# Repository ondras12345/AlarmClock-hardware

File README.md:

# AlarmClock Hardware
This repository contains hardware design files for [AlarmClock][AlarmClock].

Schematics and PCBs are designed in [KiCAD][KiCAD].

[AlarmClock]: https://github.com/ondras12345/AlarmClock
[KiCAD]: https://www.kicad.org/

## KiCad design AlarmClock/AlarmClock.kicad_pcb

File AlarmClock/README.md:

# AlarmClock
This is the main project for the whole thing. Both schematics and PCB design.

[Schematics](./AlarmClock.pdf)
[PCB](./AlarmClock-PCB.pdf)

The PCB is designed to be milled out from a single sided copper clad laminate
on a CNC machine. However, the design should also be suitable for standard
etching.

**Warning**: R27 is currently NOT included in the gcode files in `cnc/`.
However, it is quite easy to bodge in if you don't want to mess with `FlatCAM`
to fix this. Gerber files are OK.

## MCU pinout
Pin numbers in the firmware are using the convention set by the Arduino
framework. To map them to MCU pins, use the following table:

|Arduino pin    | MCU pin   |
|:--------------|:----------|
| 0             | PD0       |
| 1             | PD1       |
| 2             | PD2       |
| 3             | PD3       |
| 4             | PD4       |
| 5             | PD5       |
| 6             | PD6       |
| 7             | PD7       |
| 8             | PB0       |
| 9             | PB1       |
| 10            | PB2       |
| 11            | PB3       |
| 12            | PB4       |
| 13            | PB5       |
| A0            | PC0       |
| A1            | PC1       |
| A2            | PC2       |
| A3            | PC3       |
| A4            | PC4       |
| A5            | PC5       |

- https://www.arduino.cc/en/uploads/Main/Arduino_Uno_Rev3-schematic.pdf

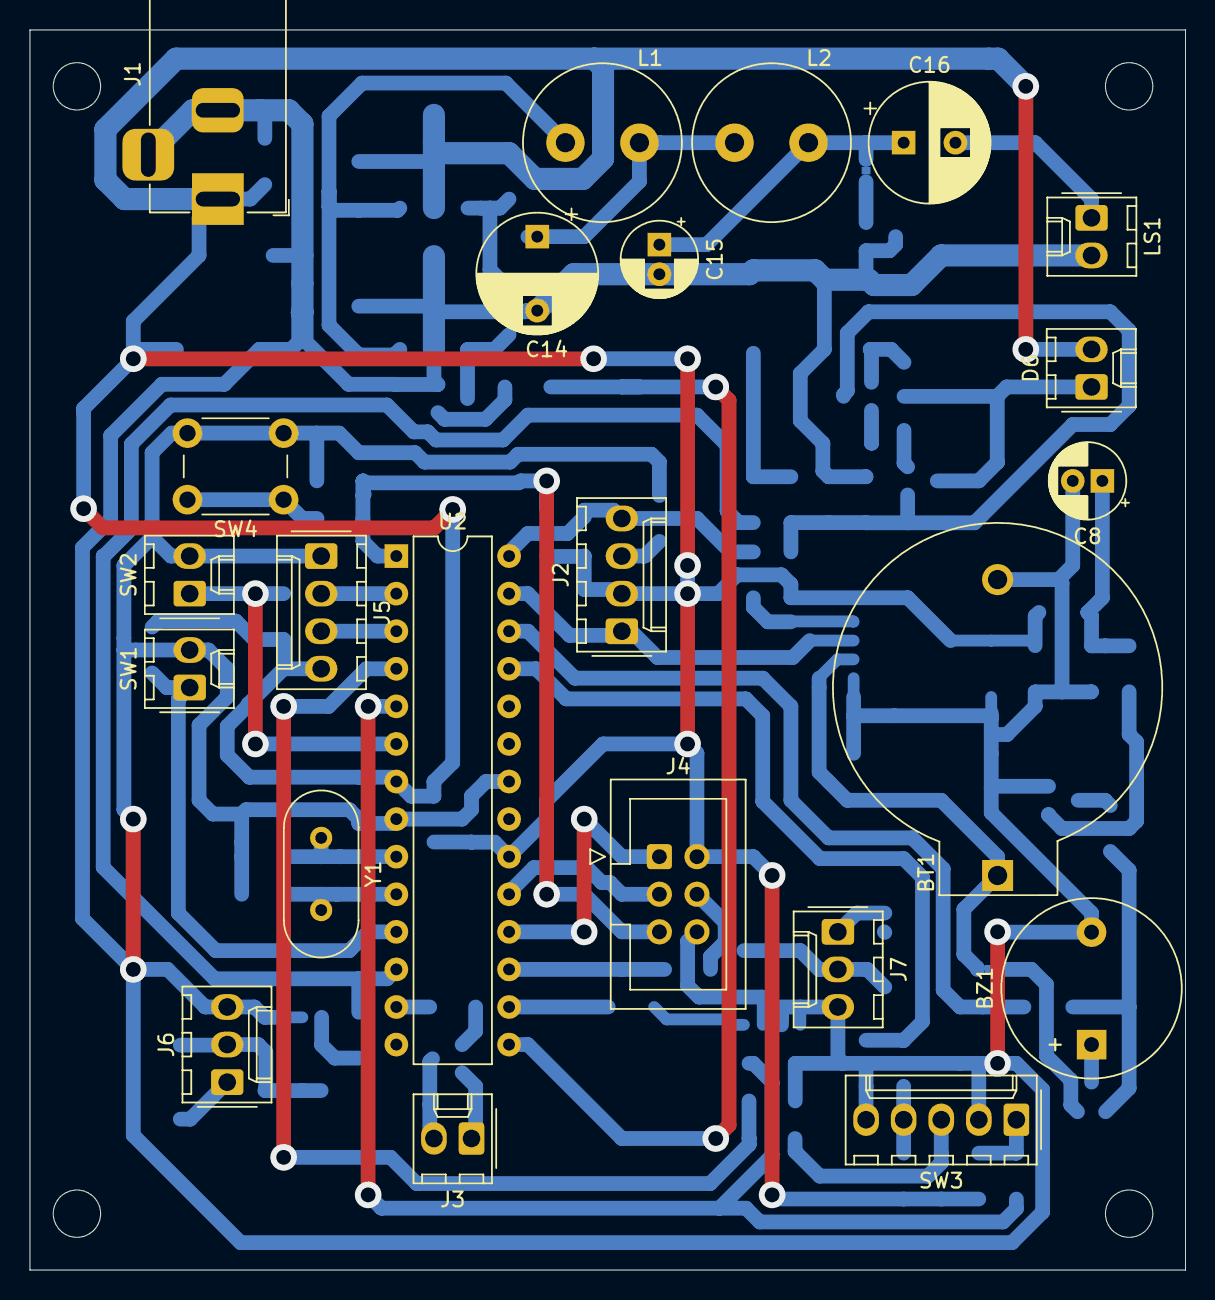
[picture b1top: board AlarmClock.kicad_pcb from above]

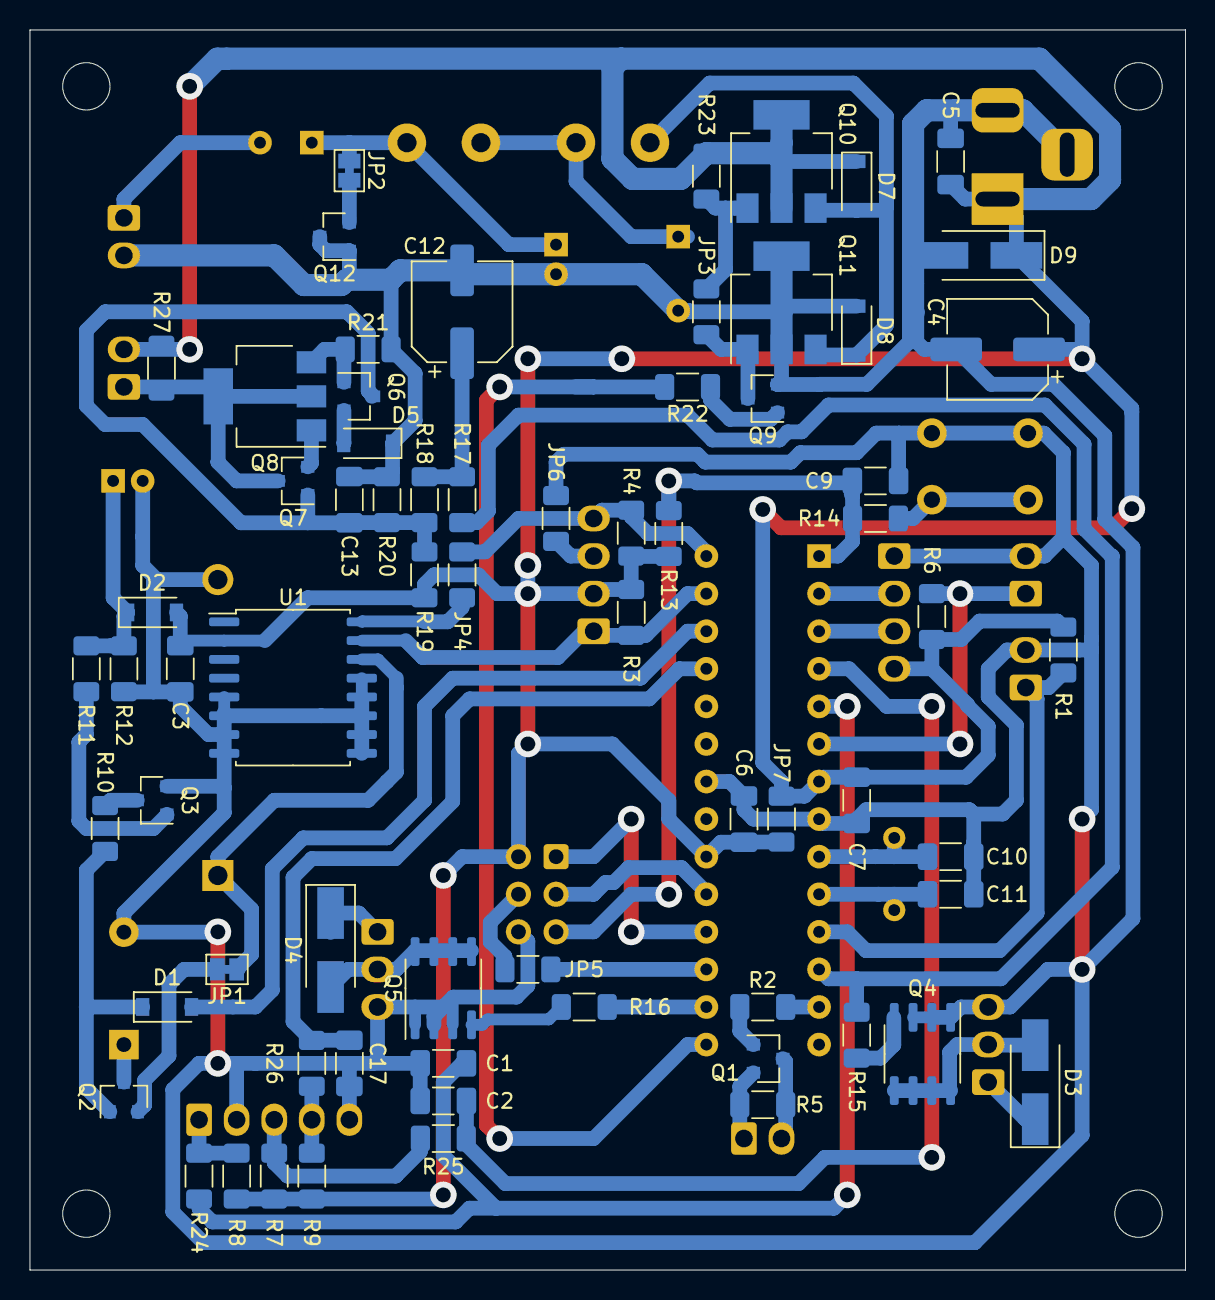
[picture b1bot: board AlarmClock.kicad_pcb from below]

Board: 2 copper layers, 78.1 x 83.8 mm, 91 parts (68 on the bottom side), 59 nets.

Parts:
BT1: CR2032; BatteryHolder_DS1092-04-B6P
BZ1: 3V3; Buzzer_12x9.5RM7.6
C1, C2: 10n; C_1206_3216Metric_Pad1.33x1.80mm_HandSolder
C3, C7, C9, C13, C17: 100n; C_1206_3216Metric_Pad1.33x1.80mm_HandSolder
C4, C12: 100u / 16V; CP_Elec_6.3x5.4
C5: 470n; C_1206_3216Metric_Pad1.33x1.80mm_HandSolder
C6: 1u / 25V; C_1206_3216Metric_Pad1.33x1.80mm_HandSolder
C8: 22u / 35V; CP_Radial_D5.0mm_P2.00mm
C10, C11: 22p; C_1206_3216Metric_Pad1.33x1.80mm_HandSolder
C14: 3u3 / 50V; CP_Radial_D8.0mm_P5.00mm
C15: 1u / 50V; CP_Radial_D5.0mm_P2.00mm
C16: 220u / 35V; CP_Radial_D8.0mm_P3.50mm
D1, D2, D5, D7, D8: 1N4148W; D_SOD-123
D3, D4, D9: 1N4007; D_SMA_Handsoldering
D6: LED; Molex_KK-254_AE-6410-02A_1x02_P2.54mm_Vertical
J1: PC-GK2.1; BarrelJack_Horizontal
J2, J5: Conn_01x04; Molex_KK-254_AE-6410-04A_1x04_P2.54mm_Vertical
J3: Conn_01x02; Molex_KK-254_AE-6410-02A_1x02_P2.54mm_Vertical
J4: AVR-ISP-6; IDC-Header_2x03_P2.54mm_Vertical
J6, J7: Conn_01x03; Molex_KK-254_AE-6410-03A_1x03_P2.54mm_Vertical
JP1, JP2: SolderJumper_2_Bridged; SolderJumper-2_P1.3mm_Bridged_Pad1.0x1.5mm
JP3, JP4, JP5, JP6, JP7: 0 ohm; R_1206_3216Metric_Pad1.30x1.75mm_HandSolder
L1: 220u; L_Radial_D10.5mm_P5.00mm_Abacron_AISR-01
L2: 100u; L_Radial_D10.5mm_P5.00mm_Abacron_AISR-01
LS1: 8 ohm; Molex_KK-254_AE-6410-02A_1x02_P2.54mm_Vertical
Q1: BC857; SOT-23
Q2: BC857B; SOT-23
Q3, Q6, Q7, Q9, Q12: BC847; SOT-23
Q4, Q5: IRL6342PbF; SOIC-8_3.9x4.9mm_P1.27mm
Q8, Q10: BCP56; SOT-223-3_TabPin2
Q11: BCP53; SOT-223-3_TabPin2
R1, R2, R6, R7, R8, R9, R10, R13, R18, R20, R24, R25, R26, R27: 10k; R_1206_3216Metric_Pad1.30x1.75mm_HandSolder
R3, R4, R5: 3k3; R_1206_3216Metric_Pad1.30x1.75mm_HandSolder
R11, R12: 100k; R_1206_3216Metric_Pad1.30x1.75mm_HandSolder
R14, R23: 330; R_1206_3216Metric_Pad1.30x1.75mm_HandSolder
R15, R16: 220; R_1206_3216Metric_Pad1.30x1.75mm_HandSolder
R17, R22: 1k; R_1206_3216Metric_Pad1.30x1.75mm_HandSolder
R19: 22k; R_1206_3216Metric_Pad1.30x1.75mm_HandSolder
R21: 6R8; R_1206_3216Metric_Pad1.30x1.75mm_HandSolder
SW1, SW2: SW_Push; Molex_KK-254_AE-6410-02A_1x02_P2.54mm_Vertical
SW3: Rotary_Encoder_Switch; Rotary_Encode_Switch_Molex_KK-254_AE-6410-05A_1x05_P2.54mm_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
SW4: SW_Push; SW_PUSH_6mm_H4.3mm
U1: DS3231M; SOIC-16W_7.5x10.3mm_P1.27mm
U2: ATmega328P-PU; DIP-28_W7.62mm
Y1: 16MHz; Crystal_HC49-U_Vertical

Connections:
+5V: C3.1, C4.1, C5.1, C6.1, C7.1, D2.2, D6.2, D7.1, D9.1, J1.1, J2.2, J4.2, J5.4, JP7.1, JP7.2, Q10.2, R1.1, R3.1, R4.1, R6.1, R7.1, R8.1, R9.1, R13.1, R19.1, R23.1, R27.1, U1.2, U2.7, U2.20
/!RST: C9.1, J4.5, R13.2, R14.2, U2.1
/BTN_snooze: R6.2, SW2.1, U2.6
/BTN_stop: R1.2, SW1.1, U2.11
/LCD_BLU: R2.2, U2.13
/MISO: J4.1, U2.18
/MOSI: JP5.2, U2.17
/RX: J5.2, U2.2
/SCK: J4.3, U2.19
/SCL: J2.4, JP4.1, R4.2, U2.28
/SDA: J2.1, R3.2, U1.15, U2.27
/TX: J5.3, U2.3
/ambient: R15.2, R17.2, U2.12
/audio: R22.2, U2.15
/buzzer: D1.2, U2.26
/enc_clk: C2.1, R25.2, U2.4
/enc_dt: C1.1, R24.2, U2.5
/enc_sw: C17.1, R26.1, U2.25
/lamp: R16.2, U2.16
GND: BT1.2, BZ1.2, C1.2, C2.2, C3.2, C4.2, C5.2, C6.2, C7.2, C8.2, C9.2, C10.1, C11.2, C12.2, C13.2, C14.2, C15.2, C17.2, D5.1, D8.2, D9.2, J1.2, J1.3, J4.6, J5.1, J6.3, J7.3, JP6.1, LS1.2, Q3.2, Q4.1, Q4.2, Q4.3, Q5.1, Q5.2, Q5.3, Q9.2, Q11.2, Q12.1, Q12.3, R12.2, R20.2, R21.2, SW1.2, SW2.2, SW3.C, SW3.S2, SW4.2, U1.5, U1.6, U1.7, U1.8, U1.9, U1.10, U1.11, U1.12, U1.13, U2.8, U2.22
unnamed: BT1.1, JP1.1, U1.14
unnamed: BZ1.1, Q2.3
unnamed: C8.1, D2.1, R11.1, R12.1
unnamed: C10.2, U2.9, Y1.1
unnamed: C11.1, U2.10, Y1.2
unnamed: C12.1, R17.1, R18.2
unnamed: C13.1, Q6.3, Q7.1, R18.1, R19.2, R20.1
unnamed: C14.1, L1.2, L2.1
unnamed: C15.1, C16.1, JP2.1, L2.2
unnamed: C16.2, LS1.1
unnamed: D1.1, Q2.1, R10.2
unnamed: D3.1, J6.1
unnamed: D3.2, J6.2, Q4.5, Q4.6, Q4.7, Q4.8
unnamed: D4.1, J7.1
unnamed: D4.2, J7.2, Q5.5, Q5.6, Q5.7, Q5.8
unnamed: D5.2, Q6.2
unnamed: D6.1, Q7.3, Q8.2, R27.2
unnamed: D7.2, D8.1, L1.1, Q10.3, Q11.3
unnamed: J2.3, JP6.2
unnamed: J3.1, Q1.2, R5.1
unnamed: J3.2, Q1.3, R5.2
unnamed: J4.4, JP5.1
unnamed: JP1.2, Q2.2
unnamed: JP2.2, Q12.2
unnamed: JP3.1, Q9.3, Q11.1
unnamed: JP3.2, Q10.1, R23.2
unnamed: JP4.2, U1.16
unnamed: Q1.1, R2.1
unnamed: Q3.1, R11.2
unnamed: Q3.3, R10.1
unnamed: Q4.4, R15.1
unnamed: Q5.4, R16.1
unnamed: Q6.1, Q8.3, R21.1
unnamed: Q7.2, Q8.1
unnamed: Q9.1, R22.1
unnamed: R14.1, SW4.1
unnamed: R8.2, R24.1, SW3.A
unnamed: R7.2, R25.1, SW3.B
unnamed: R9.2, R26.2, SW3.S1

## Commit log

2022-03-29 Add project files
2022-03-29 Annotate schematics, assign footprints, pcbnew
2022-03-29 Add data for PCB manufacture
2022-03-29 Design the PCB
2022-03-29 Populate I2C pull-up resistors
2022-03-29 Add main project schematic
2022-03-31 Fix ambient LED staying lit
2022-04-08 Update text in AlarmClock schematic
2022-04-08 Add AlarmClock-encoder
2022-04-13 Update symbol fields for BOM
2022-04-24 Add FreeCAD designs of the enclosure
